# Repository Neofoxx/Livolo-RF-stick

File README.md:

# LIVOLO-RF-Stick
A USB dongle for controlling Livolo RF switches

#### Finished product

*Front view of finished product*

*Back view of finished product*

#### PCB board view

*PCB board view*

## Description

This is a simple dongle for controling Livolo brand RF switched.
It is based around the following components:
- [PIC32MM0064GPL020s](https://www.microchip.com/wwwproducts/en/PIC32MM0064GPL020) microcontroller
- [RFM69](https://www.hoperf.com/modules/rf_transceiver/RFM69HCW.html) module
- CH340G USB-serial converter
- ABRACON [ACAG1204-433-T](https://abracon.com/datasheets/ACAG1204-433-T.pdf) ceramic antenna
- Multicomp [MCG1901](https://uk.farnell.com/multicomp/mcg1901/box-usb-plug-in-clear-polycarbonate/dp/1603603) plastic housing (Wifi dongle style)

#### Performance
Performance is about on-par with the official handheld remote.
Antenna tuning is 72nH in series with antenna, 1pF in parallel with antenna.

#### Extra info

A longer writeup can be found [here](https://neofoxx.com/post-4.html).

## Usage example

Connect to the dongle at 115200bps, 8N1.
Send commands like "COMMAND [...]\n". Commands can be either lower or uppercase.

A help command is implemented, and will printout this:
```
RF stick, for controlling Livolo switches␊
Commands:␊
HELP - Print this help
SCAN - Perform an RSSI scan of a wider area
DEBUG - Print out some diagnostic data
SNIFF [Minimum RSSI] [Timeout] - Sniff for Livolo packets.
-> RSSI should be [-115 to 0]. In practice, use -80, maybe -90 for really weak signals
-> Timeout is in miliseconds. You can put 0 for no timeout. You can always end by sending \n
TRANSMIT [Remote ID] [Keycode] [Number of repeats] - Send a packet many times
-> Remote ID is a 16-bit unsigned number
-> Keycode is a 6-bit unsigned number
-> Number of packets can be [1 to 1000]. Each one takes 8ms, fyi.
----> THIS DOES NOT VERIFY IF YOU DATA IS CORRECT. YOU HAVE TO MAKE SURE THAT YOU HAVE THE RIGHT NUMBER OF 1s!
```

Take special care when sending packets, as the switches are fussy about how many you send -> they **react differently** to how many packets you send.
- ON/OFF commands - 25 to 30 packets is kinda the ideal. If you send more than 50, weird things start happening (lights turning ON and then back OFF or vice versa)
- DIMMING commands - a minimum of 20 packets works reliably. It sometimes works with less, but it's not recommended. This means you can dim the light on in increments, by sending >=20 packets for each UP increment.

Each button on a remote send two different key codes, depending on how you press a button.
- SHORT press - send those 25-30 packets, with a keycode **X**
- LONG press - continues sending packets until release, with keycode **Y**. Used for dimming

To synchronize/bind a key, you **MUST** send the **ON/OFF** command (**SHORT press**). After you put the switch into its "synchronize/learning/binding" mode of course. The switch should respond with a single **beep** when button is bound (at least on my test switch)-

To unbind a key, you *can* send the the **ON/OFF** sequence twice (or just a longer packet), when the switch is in its "synchronize/learning/binding" mode. The switch should responded with two **beeps** when it unbinds (again, works on my test unit).
This also works with a normal remote, if you double-tap a key, though I couldn't find this functionality in the included mini-manual.

#### TLDR
1. Send "SNIFF -90 20", so get the REMOTE_ID and Keycode_ID from your existing remote
2. Send "TRANSMIT [REMOTE_ID] [Keycode_ID] 25" for ON/OFF commands
3. Send "TRANSMIT [REMOTE_ID] [Keycode_ID] [DO_YOUR_OWN_MATH]" for dimming commands. Time sending packets = (8ms * number_of_packets), or flipped, number_of_packets = total_time_in_ms / 8.

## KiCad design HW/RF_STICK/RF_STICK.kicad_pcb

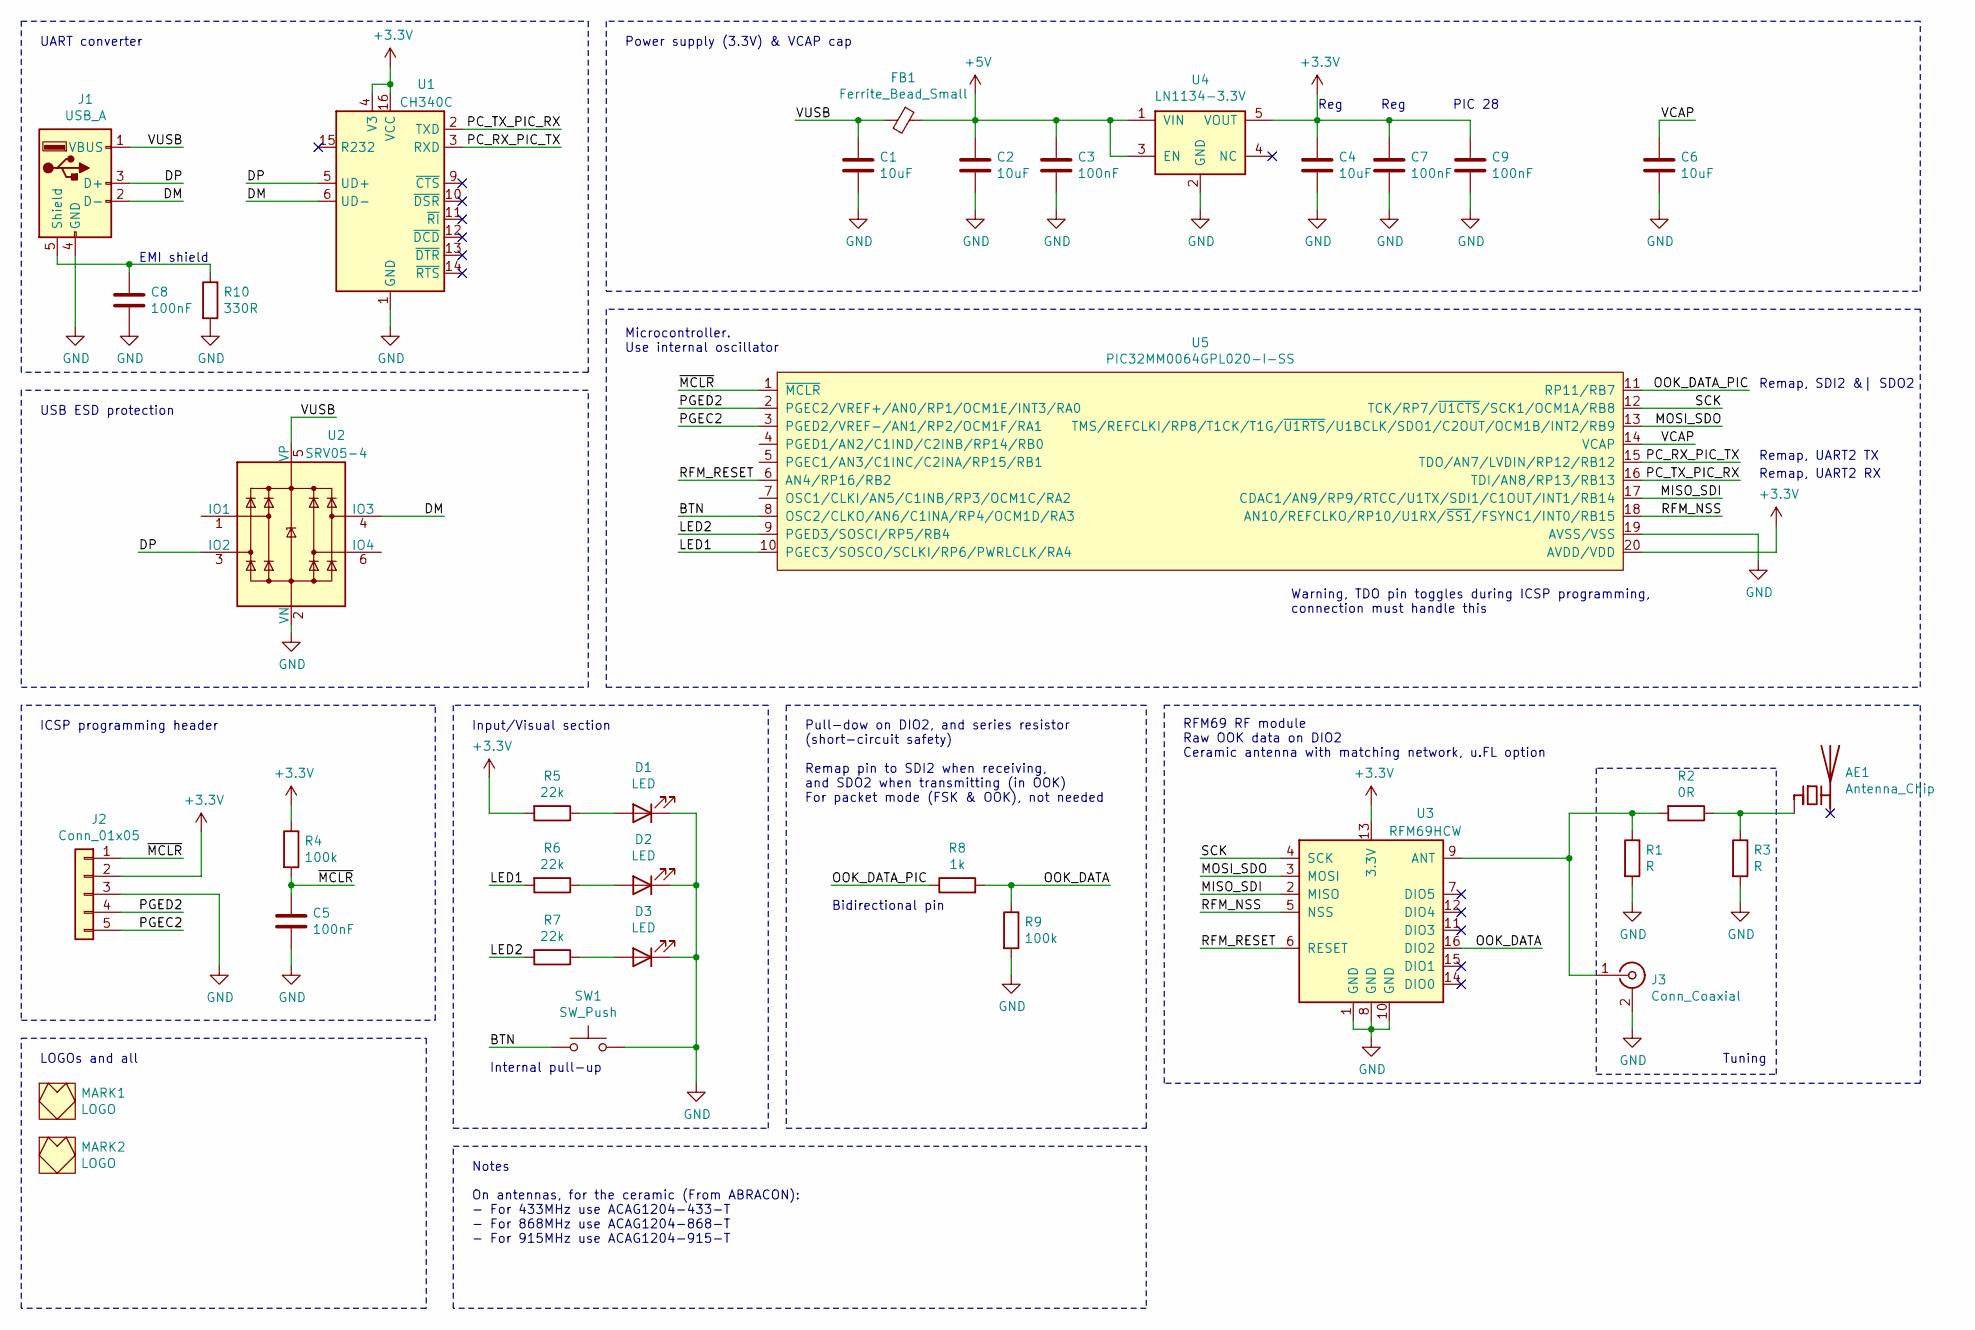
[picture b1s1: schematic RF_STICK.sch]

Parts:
AE1: Antenna_Chip; ACAG1204-433-T
C1, C2, C4, C6: 10uF; C_0805_2012Metric
C3, C5, C7, C8, C9: 100nF; C_0603_1608Metric
D1, D2, D3: LED; LED_0603_1608Metric
FB1: Ferrite_Bead_Small; L_0805_2012Metric
J1: USB_A; USB_A_PCB
J2: Conn_01x05; PinHeader_1x05_P1.27mm_Vertical
J3: Conn_Coaxial; U.FL_Hirose_U.FL-R-SMT-1_Vertical
MARK1, MARK2: LOGO; FOX_LOGO_MASK
R1, R3: R; R_0603_1608Metric
R2: 0R; R_0603_1608Metric
R4, R9: 100k; R_0603_1608Metric
R5, R6, R7: 22k; R_0603_1608Metric
R8: 1k; R_0603_1608Metric
R10: 330R; R_0603_1608Metric
SW1: SW_Push; SW_SPST_CK_KXT3
U1: CH340C; SOIC-16_3.9x9.9mm_P1.27mm
U2: SRV05-4; SOT-23-6
U3: RFM69HCW; HOPERF_RFM9XW_SMD
U4: LN1134-3.3V; SOT-23-5
U5: PIC32MM0064GPL020-I-SS; SSOP-20_5.3x7.2mm_P0.65mm_MOD

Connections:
+3V3: C4.1, C7.1, C9.1, J2.2, R4.1, R5.2, U1.4 (V3), U1.16 (VCC), U3.13 (3.3V), U4.5 (VOUT), U5.20 (AVDD/VDD)
+5V: C2.1, C3.1, FB1.1, U4.1 (VIN), U4.3 (EN)
/BTN: SW1.1, U5.8 (OSC2/CLKO/AN6/C1INA/RP4/OCM1D/RA3)
/DM: J1.2 (D-), U1.6 (UD-), U2.4 (IO3)
/DP: J1.3 (D+), U1.5 (UD+), U2.3 (IO2)
/LED1: R6.2, U5.10 (PGEC3/SOSCO/SCLKI/RP6/PWRLCLK/RA4)
/LED2: R7.2, U5.9 (PGED3/SOSCI/RP5/RB4)
/MISO_SDI: U3.2 (MISO), U5.17 (CDAC1/AN9/RP9/RTCC/U1TX/SDI1/C1OUT/INT1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)
/MOSI_SDO: U3.3 (MOSI), U5.13 (TMS/REFCLKI/RP8/T1CK/T1G/~U1RTS~/U1BCLK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)
/OOK_DATA: R8.2, R9.1, U3.16 (DIO2)
/OOK_DATA_PIC: R8.1, U5.11 (RP11/RB7)
/PC_RX_PIC_TX: U1.3 (RXD), U5.15 (TDO/AN7/LVDIN/RP12/RB12)
/PC_TX_PIC_RX: U1.2 (TXD), U5.16 (TDI/AN8/RP13/RB13)
/PGEC2: J2.5, U5.3 (PGED2/VREF-/AN1/RP2/OCM1F/RA1)
/PGED2: J2.4, U5.2 (PGEC2/VREF+/AN0/RP1/OCM1E/INT3/RA0)
/RFM_NSS: U3.5 (NSS), U5.18 (AN10/REFCLKO/RP10/U1RX/~SS1~/FSYNC1/INT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)
/RFM_RESET: U3.6 (RESET), U5.6 (AN4/RP16/RB2)
/SCK: U3.4 (SCK), U5.12 (TCK/RP7/~U1CTS~/SCK1/OCM1A/RB8)
/VCAP: C6.1, U5.14 (VCAP)
/VUSB: C1.1, FB1.2, J1.1 (VBUS), U2.5 (VP)
/~MCLR~: C5.1, J2.1, R4.2, U5.1 (~MCLR~)
GND: C1.2, C2.2, C3.2, C4.2, C5.2, C6.2, C7.2, C8.2, C9.2, D1.1 (K), D2.1 (K), D3.1 (K), J1.4 (GND), J2.3, J3.2 (Ext), R1.2, R3.2, R9.2, R10.2, SW1.2, U1.1 (GND), U2.2 (VN), U3.1 (GND), U3.8 (GND), U3.10 (GND), U4.2 (GND), U5.19 (AVSS/VSS)
unnamed: AE1.1 (FEED), R2.1, R3.1
unnamed: C8.1, J1.5 (Shield), R10.1
unnamed: D1.2 (A), R5.1
unnamed: D2.2 (A), R6.1
unnamed: D3.2 (A), R7.1
unnamed: J3.1 (In), R1.1, R2.2, U3.9 (ANT)

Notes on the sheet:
Reg
PIC 28
Remap, UART2 TX
Remap, SDI2 &| SDO2
Remap, UART2 RX
UART converter
USB ESD protection
Microcontroller. Use internal oscillator
Power supply (3.3V) & VCAP cap
Bidirectional pin
Internal pull-up
ICSP programming header
Input/Visual section
Tuning
RFM69 RF module Raw OOK data on DIO2 Ceramic antenna with matching network, u.FL option
Pull-dow on DIO2, and series resistor (short-circuit safety) Remap pin to SDI2 when receiving, and SDO2 when transmitting (in OOK) For packet mode (FSK & OOK), not needed
LOGOs and all
Notes
On antennas, for the ceramic (From ABRACON): - For 433MHz use ACAG1204-433-T - For 868MHz use ACAG1204-868-T - For 915MHz use ACAG1204-915-T
Warning, TDO pin toggles during ICSP programming, connection must handle this
EMI shield

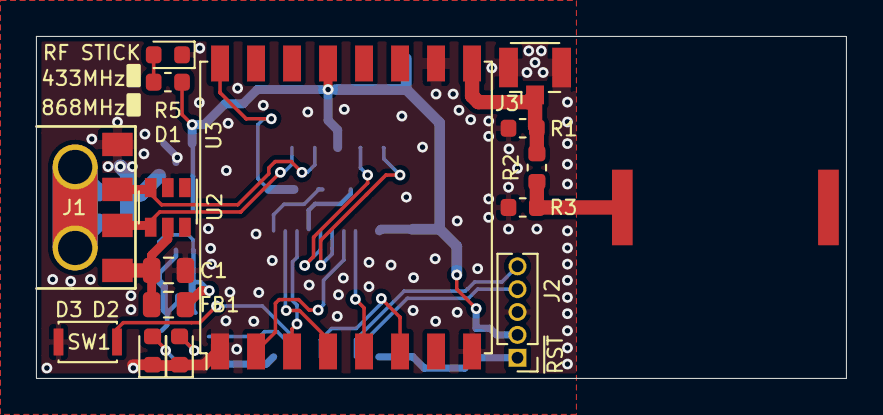
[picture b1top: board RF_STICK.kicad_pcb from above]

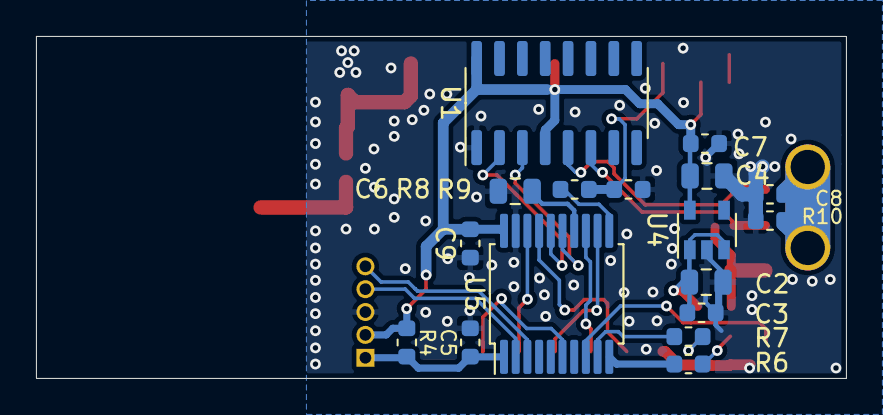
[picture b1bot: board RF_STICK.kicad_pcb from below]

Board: 2 copper layers, 45.0 x 19.0 mm, 35 parts (18 on the bottom side), 28 nets.

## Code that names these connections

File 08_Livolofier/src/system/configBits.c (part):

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												// Hence this hack, to have it aligned, since the definition shifts by 15, instead of 16...
	| (0b0 << _FDEVOPT_FVBUSIO_POSITION)	// VBUSON pin is controlled by port function, not USB
	| (0b0 << _FDEVOPT_FUSBIDIO_POSITION)	// USBID pin is controlled by port function, not USB	
	| (0b1 << _FDEVOPT_ALTI2C_POSITION)	// SDA1 and SCL1 are on pins RB8 and RB9											
	| (0b1 << _FDEVOPT_SOSCHP_POSITION);	// SOSC operated in Normal Power mode

const uint32_t __attribute__((section (".SECTION_FICD"))) temp_ficd =
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const uint32_t __attribute__((section (".SECTION_FOSCSEL"))) temp_foscsel =
	0xFFFF2828
	| (0b01 << _FOSCSEL_FCKSM_POSITION)		// Clock switching ENABLED, Fail-Safe clock monitor disabled - needed for switch to different clock speed
	| (0b0 << _FOSCSEL_SOSCSEL_POSITION)	// External clock connected to SOSCO pin (RA4 RB4 controlled by I/O PORTx)
	| (0b1 << _FOSCSEL_OSCIOFNC_POSITION)	// System clock not on CLKO pin, operates as normal I/O
	| (0b11 << _FOSCSEL_POSCMOD_POSITION)	// Primary oscillator is disabled
	| (0b0 << _FOSCSEL_IESO_POSITION)		// Two-speed Start-up is disabled
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const uint32_t __attribute__((section (".SECTION_AFOSCSEL"))) temp_afoscsel =
	0xFFFF2828
	| (0b01 << _FOSCSEL_FCKSM_POSITION)		// Clock switching ENABLED, Fail-Safe clock monitor disabled - needed for switch to different clock speed
	| (0b0 << _FOSCSEL_SOSCSEL_POSITION)	// External clock connected to SOSCO pin (RA4 RB4 controlled by I/O PORTx)
	| (0b1 << _FOSCSEL_OSCIOFNC_POSITION)	// System clock not on CLKO pin, operates as normal I/O
	| (0b11 << _FOSCSEL_POSCMOD_POSITION)	// Primary oscillator is disabled
	| (0b0 << _FOSCSEL_IESO_POSITION)		// Two-speed Start-up is disabled
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
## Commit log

2021-03-27 First commit, just for backup
2021-04-02 Mid-work commit
2021-04-02 Mid-work commit. Interrupts work, command parsing works, etc
2021-04-30 Working version
2021-04-30 Added README and pictures
